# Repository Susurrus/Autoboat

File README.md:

Autoboat
========

This repository contains code used for running the Autoboat, a 20' robotic surface vessel currently in development at the University of Santa Cruz under the directive of Professor Gabriel Elkaim. This respository is therefore likely to be of little interest to outsiders, though much of the support code is fairly modular. Groundstation software for this vessel is provided via the QGroundControl project and is not contained within this repository.

File layout
-----------
 * CAD - Contains CAD designs of both mechanical and electrical systems. The mechanical systems have been modeled in SolidWorks 2010 while the electrical schematics have been generated using Eagle 6.
 * Code - This contains the software used for controlling the boat. Primarily Simulink and C control its operation and MATLAB and Python scripts assist in data parsing and analysis
 * Documentation - Various documents regarding this project are stored in this directory.

Main project
------------

The main project code is housed within /Code/Primary_node/primary_node.mdl and /Code/basic\_model/Boat\_sim.mdl, both Simulink 2011b models.

Boat_sim.mdl provides a simulator for testing my vehicle/environmental model and the vehicle controllers. It can run solely on a computer or via a UDP port provide the vehicle/environmental simulation to an external controller for use in Hardware-in-the-Loop (HIL) testing. Relies on the MicroSimulink library (<https://github.com/Susurrus/MicroSimulink-Library>).

primary_node.mdl contains all of the controller logic for the primary controller. It is organized as hardware dependent code that wraps the main controller block that is shared with Boat_sim.mdl (via the make.m script). This is designed to run aboard a CANode with the dsPIC33FJ256GP710A onboard along with a custom shield for providing connections to peripherals. It depends on both the MicroSimulink library (<https://github.com/Susurrus/MicroSimulink-Library>), Lubin's PIC blockset (<http://www.kerhuel.eu/wiki/Simulink_-_Embedded_Target_for_PIC>), and the ECAN blockset (<https://github.com/Susurrus/ECAN_dspic>). All of these dependencies must be correctly installed and on the path along with Microchip's xc16 compiler for this project to compile to an executable.

The toolboxes required by the various models are the Aerospace Blockset, MATLAB, MATLAB coder, Simulink, and Simulink Coder.

Code generation of the MATLAB projects requires a supported compiler [www.mathworks.com/support/compilers/R2011b] crosoft's Visual Studio 2010 is also required in order to compile the project or the Windows SDK 7.1 or newer. Both are available for free online.

In addition to these Simulink libraries, the MAVLink C library for the SeaSlug must be installed. Download it from <https://github.com/mavlink/mavlink> into the same directory that this repository is contained in so that it looks like:
/MicroSimulink-Library
/ECAN_dspic
/Autoboat
/mavlink

You'll need Python 2.6+ to run the MAVLink generator from within the mavlink directory:

```$ python mavgen.py --lang=C --wire-protocol=1.0 -o include ../Autoboat/Code/Libs/MAVLink/seaslug.xml```

This will put the MAVLink code for the SeaSlug dialect into ```/mavlink/include``` where it can be referenced by primary_node.mdl.

The current version of MAVLink will not compile with the xc16 compiler unless the ```stdint.h``` header file within the xc16 includes directory is duplicated as an ```inttypes.h``` file.
 
Further documentation
---------------------

A wiki has been hosted to provide details on this project at <http://byron.soe.ucsc.edu/autoboat/wg2/>.

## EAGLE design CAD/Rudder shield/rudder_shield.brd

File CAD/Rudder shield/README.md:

This board is designed for V2.x of the CAN node that exists in the ASL repository. I provides connections for integrating an analog potentiometer (with a 21Hz lowpass filter on it) and two open-drain limit switches. Additionally it has a connection for a stepper motor driver board.

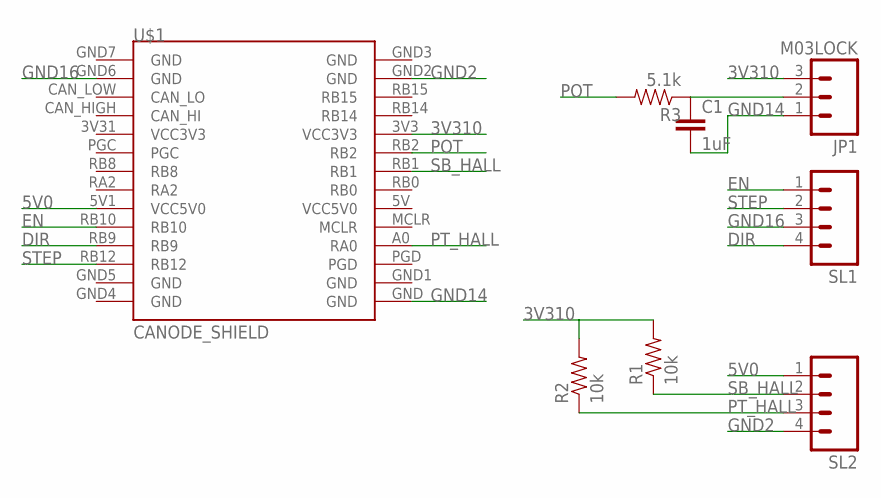
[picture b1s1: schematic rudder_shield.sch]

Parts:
C1: 1uF; 1206
JP1: M03LOCK; 1X03_LOCK
R1, R2: 10k; 0805
R3: 5.1k; 0805
SL1, SL2: M04LOCK; 1X04_LOCK
U$1: CANODE_SHIELD

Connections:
3V310: JP1.3, R1.2, R2.2, U$1.3V3 (VCC3V3)
5V0: SL2.1, U$1.5V1 (VCC5V0)
DIR: SL1.4, U$1.RB9
EN: SL1.1, U$1.RB10
GND2: SL2.4, U$1.GND2 (GND)
GND14: C1.2, JP1.1, U$1.GND
GND16: SL1.3, U$1.GND6 (GND)
unnamed: C1.1, JP1.2, R3.1
POT: R3.2, U$1.RB2
PT_HALL: R2.1, SL2.3, U$1.A0 (RA0)
SB_HALL: R1.1, SL2.2, U$1.RB1
STEP: SL1.2, U$1.RB12

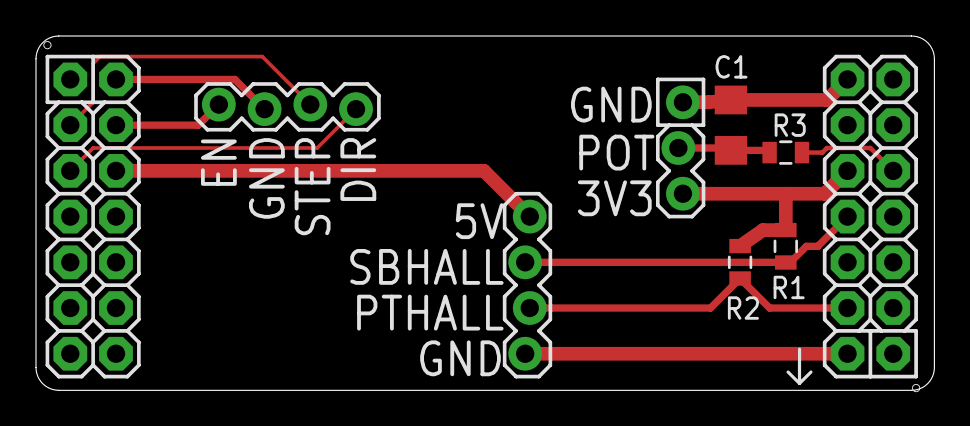
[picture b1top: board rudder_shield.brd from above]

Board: 2 copper layers, 49.9 x 19.7 mm, 8 parts (0 on the bottom side), 12 nets.

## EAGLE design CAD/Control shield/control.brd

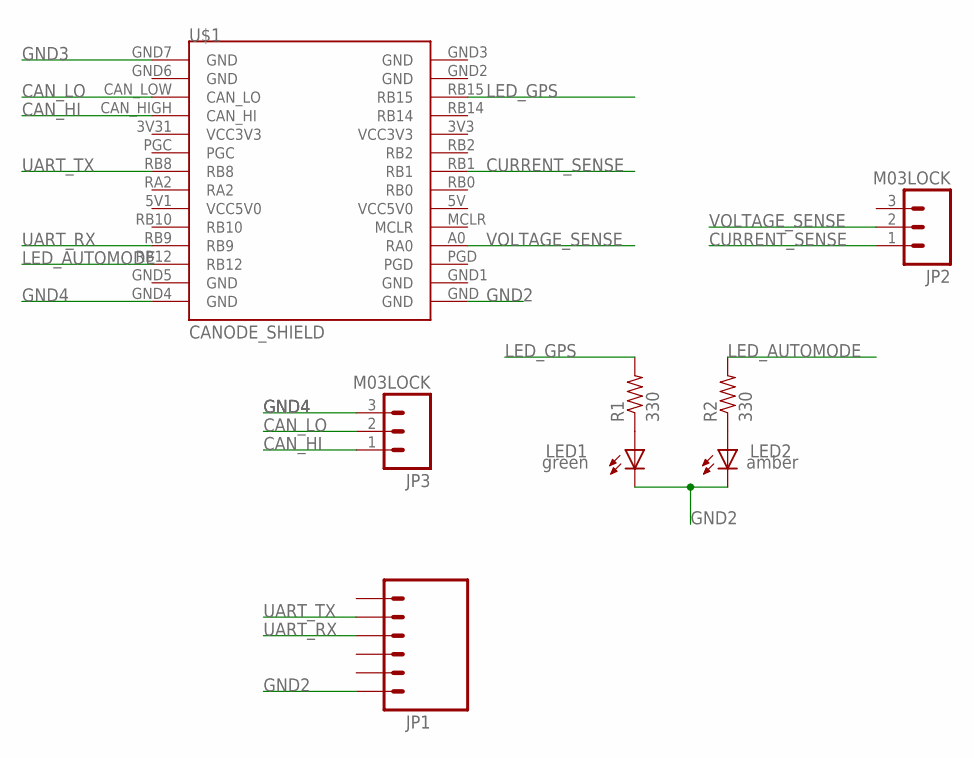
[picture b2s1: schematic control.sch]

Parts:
JP1: M06LOCK; 1X06_LOCK
JP2, JP3: M03LOCK; 1X03_LOCK
LED1, LED2: LED1206; LED-1206
R1, R2: 330; 0805
U$1: CANODE_SHIELD

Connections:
CAN_HI: JP3.1, U$1.CAN_HIGH (CAN_HI)
CAN_LO: JP3.2, U$1.CAN_LOW (CAN_LO)
CURRENT_SENSE: JP2.1, U$1.RB1
GND2: JP1.1, LED1.C, LED2.C, U$1.GND
GND3: U$1.GND7 (GND)
GND4: JP3.3, U$1.GND4 (GND)
LED_AUTOMODE: R2.2, U$1.RB12
LED_GPS: R1.2, U$1.RB15
unnamed: LED1.A, R1.1
unnamed: LED2.A, R2.1
UART_RX: JP1.4, U$1.RB9
UART_TX: JP1.5, U$1.RB8
VOLTAGE_SENSE: JP2.2, U$1.A0 (RA0)

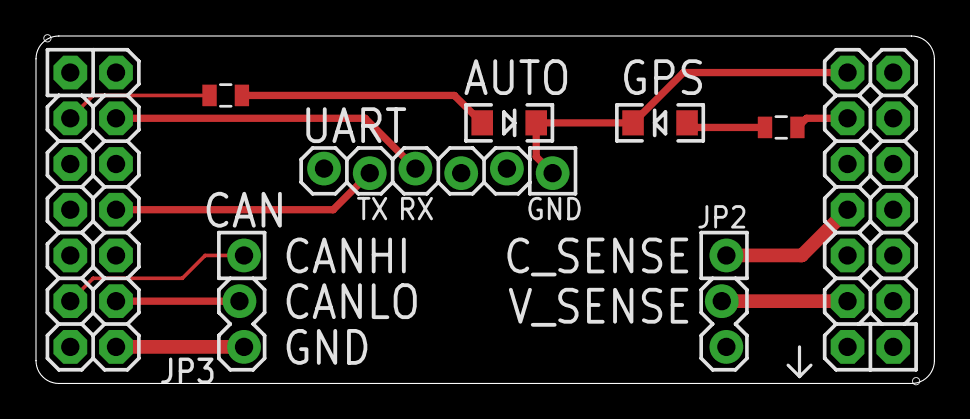
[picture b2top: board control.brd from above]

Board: 2 copper layers, 49.9 x 19.3 mm, 8 parts (0 on the bottom side), 12 nets.

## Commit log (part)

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2014-05-22 Code/PrimaryNode: Initialize acutator commands to sane values. Prevents warnings when controller_custom() is commented out for debugging or if it never set a value.
2014-05-23 Code/Libs: Fixed corruption bug with Uart1 code. Interrupts had CB_Read*()/CB_Write*() function calls that could interrupt other calls of the same type. These functions are no reentrant, so the indic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
2014-05-23 Code/Libs: Copied corruption fixes from Uart1 to Uart2 library.
2014-06-11 Updated MAVLink with new version, QGC needs this newer version now.
2014-06-13 Primary node: Restore the original message transmission rates.
2014-06-13 Primary node: Removed variables now unused because MAVLink corruption is no longer being detected.
2014-06-15 Primary node: Removed +-17 degree deadband around 0.
2014-08-01 Added a bunch of useful MATLAB scripts. Mostly used for offline data analysis.
2014-10-14 Improve .gitignore
2014-10-14 dynamic_plots now supports spacebar for pausing/playing the animation.
2014-10-14 Add some documentation for what to do after simulation.
2014-10-20 Added the AttitudeNode for providing orientation data.
    Will eventually do full IMU calculations using the MPU6050 and MAG3110 sensors.
2014-10-24 Use new IMU lib and switch to interrupts for IMU data.
2014-10-29 Updated MPU lib.
2014-11-03 Updated code to support new quaternion imu+gyro data.
    Plant now generates attitude vectors and gyro data.
    Controller uses KPsiDot as its gain on the yaw-rate feed-forward.
    HIL_sim is the only thing that has not yet been updated.
2014-11-04 HIL now uses quaternion data as the real vehicle does.
2014-11-09 Fixed improper roll correction.
    Didn't realize that the visualization was an artificial horizon, so it's from the viewpoint of the vehicle, not the ground.
2014-11-09 Forgot to convert to fixed-point for transmiting IMU data over CAN.
2014-11-10 Remove unused pin mapping.
2014-11-10 Add a simulator of the plant.
    Allows for testing the plant model by just running it open-loop on live data.
2014-11-11 Updated MAVLink version.
2014-11-12 Fix AddressError trap instigated by MAVLink code upgrade.
2014-11-12 Fix error counting for MAVLink.
2014-11-13 Make Ecan1Transmit() return a bool.
    And modify NodeTransmitStatus() to forward it on.
2014-11-13 Fix warnings with Ethernet library.
2014-11-20 Correct the parsing of PGN126992.
    Previous output of usecsSinceEpoch was incorrect and only the usecsSinceMidnight. This has since
    been corrected.
2014-11-21 Fix doc comment for static_plots.
2014-11-21 Minor docs fix.
2014-11-25 Update waypoint tracks.
2014-11-25 Misc. cleanup.
    Remove unused nextTrack/resetTrack inputs.
    Remove unnecessary MissionInit() call.
    Update Controller model.
2014-11-26 Comment out the time consuming part of PlotTrack.
2014-12-02 Update Replay_sim to the newest Controller.mdl.
2014-12-04 Add GpsOffsetCorrectionEnable parameter to the controller.
2014-12-04 Default to using GPS offset correction.
2014-12-08 Increase switchDistance and maxDownPath*.
    This reduces overshoot during waypoint transitions.
2014-12-11 Refactor L2+ block.
    Removed dead code.
    Improved comments.
    Reorganized code.
2014-12-11 Minor edits/refactoring.
2014-12-11 Remove initial point support.
    It is potentially broken as it's never been tested.
    And it's unclear how to implement in a way that allows for different waypoint sets since
    the code latches values at initialization.
2014-12-14 Make sure wp0 and wp1 are always in view as well.
2014-12-15 Updated since the ECAN1 library has been removed.
    Added a new Ecan1RcNodeHelper file that has a single function that converts library calls
    for the ECAN1 peripheral to MATLAB-compatible function calls. This is then called in the
    Simulink through a C-function call block. Functionality should be equivalent.
2014-12-15 Fix labeling error.
2014-12-16 Various L2+ refactoring/bug fixes.
2015-01-07 Output the true heading in the ATTITUDE message.
2015-01-08 Rotated the IMU so it points forward.
2015-01-09 Use YawPitchRoll angles instead of Euler angles.
2015-01-20 Set correct length and fix tests for PGN127245.
    Invalid values are specified as the maximum positive storable value in NMEA2000, which
    wasn't set correctly for the angleOrder or position fields.
2015-01-20 Added UsecondsSinceEpoch() to Nmea2000 library.
    Allows the calculations to be easily testable.
    Tests have been added.
    Function has been corrected to not subtract off leap days, which it should never
    have been doing.
2015-01-20 Use 0s as invalid date/time placeholders instead.
    Makes more sense than UINT*_MAX, which I used because NMEA2000 uses that. I think
    using 0s is more intuitive.
2015-01-27 Clarify some MATLAB parameters.
2015-01-28 Make the 2-waypoint test actually in the harbor.
2015-01-28 Add animation scripts for the full and replay sims.
    They have similar functionality as dynamic_plots.m
2015-01-28 Allow for scaling the boat/rudder drawings.
2015-01-28 Start the boat at the harbor loading ramp.
2015-01-28 Fix GPS offset correction.
    And add a bunch of debugging data.
2015-01-28 Improve the Replay sim. Too many changes to list.
2015-02-03 Correct styling of asterixes.
2015-02-04 Add a script that updates both this project and a QGC project with up-to-date MAVLink headers.
2015-02-04 Switch CONTROLLER_DATA over to using fixed-point types.
    Reduced the packet data size from 114 to 70, which can be transmit @100Hz.
2015-02-06 Don't use C99 for-loops to allow for compilation with XC16.
2015-02-09 Updated MAVLink library.
2015-02-09 Update the mav_corrup_test so it compiles.
2015-02-12 Update MAVLink.
2015-02-12 Add method for converting timesteps to newData signal.
2015-02-12 Make update_mavlink.sh more robust.
2015-02-13 Split the MAVLink streams for the groundstation and logger.
    Channel 0 is the groundstation and channel 1 is the logger.
    This has broken the parameter value output that was being used to transmit over to QGC which
    will be fixed shortly.
    Also UART2 is now used for the datalogger and mapped to the extra FTDI pinout on the PrimaryNode shield.
2015-02-13 Add the start of the ballast node code.
2015-02-13 Fix the parameter transmission code when switching to autonomous mode.
2015-02-13 Update the docs field yaw/pitch/roll in the Tokimec messages.
2015-02-13 Make Bash scripts require it and be executable.
2015-02-17 Add a function to determine the current actuator commands.
2015-02-17 Add a non-sorting unique() function to MATLAB.
2015-02-17 Adding a manual for the SeaSlug.
2015-02-18 Prep the replay sim for using the CONTROLLER_DATA message.
    Also improved user input handling, so the user can cancel.
2015-02-19 Move MATLAB scripts and libs to proper directories.
    Also deleted unused old file.
2015-02-20 Update tests and clarify docs for Euler rate calculations.
2015-02-20 Correct GPS output to be in the [-pi..pi] range.
    This was breaking things oddly as the HIL sim does no conversion besides datatypes.
2015-02-24 Update script for new messages.
2015-02-25 Make dynamic_plots work for datalogger logs.
    Still bugs in it.
2015-02-25 Fix incorrect data scaling.
2015-02-25 Use the CONTROLLER_DATA messages in Replay_sim.
2015-02-26 Remove useless plot.
2015-02-26 Decided not to set manual mode when the emergency controller is on.
    This actually triggers QGC to transmit controll messages. I'd prefer that doesn't happen.
    So to determine if the override is being used to override autonomous control, just check
    the custom_mode member of the HEARTBEAT message.
2015-02-27 Fix decoding of HDOP/VDOP data from PGN129539
2015-02-27 Make sure HDOP/VDOP are invalid at initialization.
2015-02-27 Output the HDOP on the new CONTROLLER_DATA message.
2015-03-02 Fix RESET/STATUS triggers not working correctly on startup.
2015-03-03 Add return to base functionality.
    This doesn't actually drive anywhere, but instead centers the rudder and kills the throttle.
2015-03-03 Add back the GPS_INVALID status bit but keep a GPS_DISCON reset bit.
    Also limit RTB functionality to GPS or GCS disconnections or e-stops.
2015-03-03 Added code/data/component location information to the operating manual.
2015-03-04 Add missing spacer page.
2015-03-06 Fix function prototype.
2015-03-06 Updated launch parts checklist.
2015-03-07 Improve debugging output from the HIL node.
    Detect if the IMU, GPS, or DST800 are transmitting and sit in an error state if so.
    Make the internal code copy the PrimaryNode more closely for consistency.
    Don't output RC status messages when the RC node is connected.
2015-03-07 Add a bunch more reset flags and expand the criteria for an RTB event.
2015-03-07 Clarify some points about HIL simulation.
2015-03-09 Change the HIL node to transmit at the same rates the GPS now does.
2015-03-09 Remove unused constant.
2015-03-09 Detect the rudder node based on its NODE_STATUS message.
2015-03-09 Allow for the primary controller to work even when the system is in a reset state.
2015-03-09 Make things a little more smooth when power cycling the controller.
2015-03-10 Use new wpReachedIndex to tell QGC to say what waypoint transition happened.
2015-03-11 Rename Heading to Course, which is more correct.
2015-03-11 Output the NAV_CONTROLLER_OUTPUT message at 2Hz.
    This provides the crosstrack error data to QGC.
2015-03-12 Don't use the starting-point logic to get to Waypoint 0.
    Instead we want to rely on the L2+ logic to guide us onto the line segments.
    This was also made redundant since the boat can drive itself pretty well now.
2015-03-12 Correct the BearingToNextWaypoint function.
2015-03-14 Don't always report YAW_POS capabilities, as they're dependent on the rudder subsystem.
    Also refactor a little bit.
2015-03-14 Update MAVLink version.
2015-03-15 Added the LED, and status/error bit info to the manual.
2015-03-15 Add details about storing the boat and final launch prep.
2015-03-19 Add audio output for crosstrack error and waypoint distance.
    Repeats every 30s after a waypoint transition while autonomous and not having errors.
2015-03-19 Meant to switch the TStar parameter to 12 in 423aaa.
2015-03-25 Output the true enabled state of the motor.
2015-03-26 Put the electronics power info in MAIN_POWER as well.
2015-03-26 Switch MAIN_POWER to use mA and mV for more precision.
2015-03-26 Correct details for People of Interest.
2015-03-30 Lower the sensitivity on the motor stall checking code.
2015-03-31 Add an NMEA2000 Fast Packet parser.
2015-04-01 Fix bug with NMEA2000 Fast Packet decoding.
2015-04-06 Add solar voltage and current power output to MAIN_POWER.
2015-04-06 Add all 3 accelerometers to the CONTROLLER_DATA message.
2015-04-07 Support variable-length fast packets.
2015-04-07 Output the number of satellites used by the GPS over MAVLink.
2015-04-07 Renamed hex2char and added an inverse function.
2015-04-07 Transmit the usage % of the datalogger and groundstation channels at startup.
2015-04-08 Add the ltp2lla() function for generating global coordinates from local ones.
    Also improve code docs.
2015-04-08 Support LOCAL_OFFSET_NED messages.
    Also improve error checking. Now we emit errors for unsupported mission coordinate frames and
    if missions arrive out of sequence.
2015-04-11 Only ever set the autonomous throttle command to the manual one.
2015-04-13 Move the waypoint switchin logic out of the L2+ block.
2015-04-14 Remove support for the DSP3000 custom messages.
    No longer used.
2015-04-14 Remove dead HILD code.
2015-04-14 Add plot_sim.m to replace the old PlotTrack.m
2015-04-18 Add KPsiDot to the PD controller with its own parameter.
2015-04-30 Add actual throttle/rudder values to the CDATA message.
2015-05-12 Correct rudder dynamics.
    Going through calculations I found a very good fit to be 0.08s delay and 0.45rad/s slew limit.
2015-06-03 Add/change some missions.
2015-06-03 Remove out-of-date task list.
2015-06-03 Made the single line harbor run a little longer.
2015-06-03 Switch to starting in the harbor facing north.
